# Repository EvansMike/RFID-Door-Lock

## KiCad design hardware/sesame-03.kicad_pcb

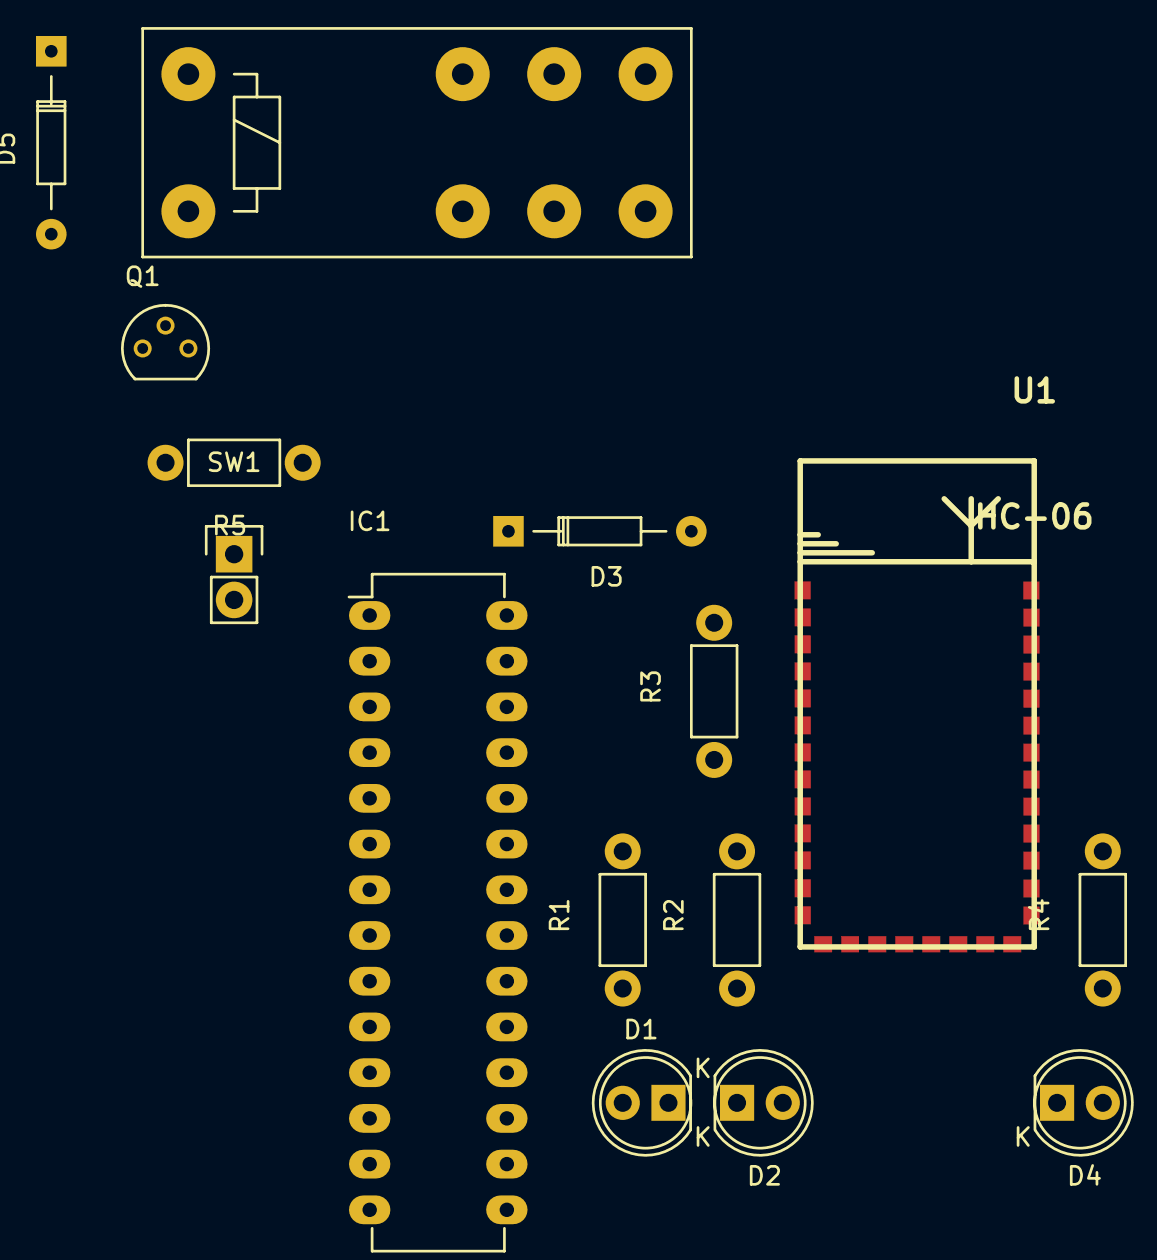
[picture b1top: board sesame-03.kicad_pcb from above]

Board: 2 copper layers, 15 parts (0 on the bottom side), 17 nets, no tracks yet.

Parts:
D1, D2, D4: LED; LED-5MM
D3, D5: 1N4148; Diode_DO-35_SOD27_Horizontal_RM10
IC1: ATMEGA8-P; DIP-28_W7.62mm_LongPads
Q1: PN2222A; TO-92_Molded_Narrow
R1, R2: 330R; Resistor_Horizontal_RM7mm
R3, R5: 3K3; Resistor_Horizontal_RM7mm
R4: 470R; Resistor_Horizontal_RM7mm
RL1: RM50-xx11; Relay_SPDT_Schrack-RT1_RM5mm
SW1: SW_PUSH_SMALL_H; Pin_Header_Straight_1x02
U1: HC-06; HC-05

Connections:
+3V3: R3.1, U1.12
+5V: IC1.7, IC1.20
GND: D1.1, D2.1, D4.1, IC1.8, IC1.22, Q1.1, SW1.1, U1.13, U1.21
unnamed: D1.2, R1.1
unnamed: D2.2, R2.1
unnamed: D3.1, IC1.3
unnamed: D3.2, R3.2, U1.2
unnamed: D4.2, R4.1
unnamed: D5.1, RL1.A1
unnamed: D5.2, Q1.3, RL1.A2
unnamed: IC1.1, SW1.2
unnamed: IC1.2, U1.1
unnamed: IC1.23, R1.2
unnamed: IC1.26, R2.2
unnamed: IC1.28, R5.1
unnamed: Q1.2, R5.2
unnamed: R4.2, U1.24

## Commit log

2018-06-01 Removed old repo completeley.
    The direction I was taking was overkill for this project. I could probably
    use an ATtiny of some sort for this as the required pin count does
    not warrant a ATmega.
2018-06-01 Clean up code.
2018-06-01 Add kikad files,
2018-06-02 removed generated files from git.
2018-06-02 Generate BT PIN from last 4 digits of master card.
2018-06-02 modified: ../README.asc
2018-06-02 Typo.
2018-06-02 Add more to README.
2018-06-02 Bug#177
    - Connect reader LED and use it indicate success
    - Connect reader beeper and use it to indicate failure.
2018-06-02 Don't clobber current setting on PORTD.
2018-06-02 I really should test BEFORE I push.
2018-06-02 Remove bogus files,
2018-06-02 new file: doc/sesame_manual.asc
2018-06-03 Spellin'
2018-06-03 Make most functions static. Some line spacing.
2018-06-03 modified: ../README.asc modified: open-sesame.c
2018-06-03 Add some optimiseations in the Makefile, Code shrunk by 1748 bytes
2018-06-04 Added CRLF to messages.
2018-06-05 Ooops. I wasn't setting the BT PIN on first card.
2018-06-05 Bug#180 Add factory reset switch.
2018-06-05 Bug#180 Move PORTD init stuff.
2018-06-05 Bug#180 Do the factory reset stuff.
2019-04-27 Put LED colours on schematic.
2019-04-27 Add missing +5V relay supply.
2019-04-27 Add missing power regulator and connector.
2019-04-27 Remove beep and LED stuff. Did't really work.
2019-05-02 Increase text buffer length by 1
    Some de-crufting.
